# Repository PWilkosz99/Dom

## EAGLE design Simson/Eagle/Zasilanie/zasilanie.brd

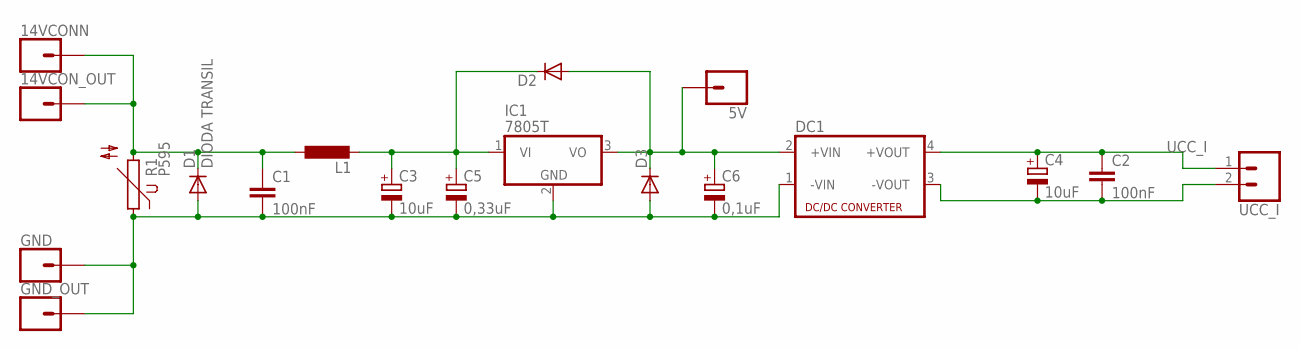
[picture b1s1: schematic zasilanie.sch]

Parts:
5V, 14VCONN, 14VCON_OUT: CONN_01PTH_LONGPAD; 1X01_LONGPAD
C1, C2: 100nF; C025-024X044
C3, C4: 10uF; E2,5-7
C5: 0,33uF; E2,5-7
C6: 0,1uF; E2,5-7
D1: DIODA TRANSIL; DO41-10
D2, D3: 1N4004; DO41-10
DC1: NME
GND: CONN_01PTH_LONGPAD; 1X01_LONGPAD
GND_OUT: CONN_01PTH_LONGPAD; 1X01_LONGPAD
IC1: 7805T; TO220H
L1: L-EUTJ6-U1; TJ6-U1
R1: P595
UCC_I: CONN_02LOCK; 1X02_LOCK

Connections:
GND: C1.2, C3.-, C5.-, C6.-, D1.A, D3.A, DC1.1 (-VIN), GND.1, GND_OUT.1, IC1.2 (GND), R1.1
GND_I: C2.2, C4.-, DC1.3 (-VOUT), UCC_I.2
unnamed: C3.+, C5.+, D2.C, IC1.1 (VI), L1.2
unnamed: 5V.1, C6.+, D2.A, D3.C, DC1.2 (+VIN), IC1.3 (VO)
unnamed: 14VCONN.1, 14VCON_OUT.1, C1.1, D1.C, L1.1, R1.2
UCC_I: C2.1, C4.+, DC1.4 (+VOUT), UCC_I.1

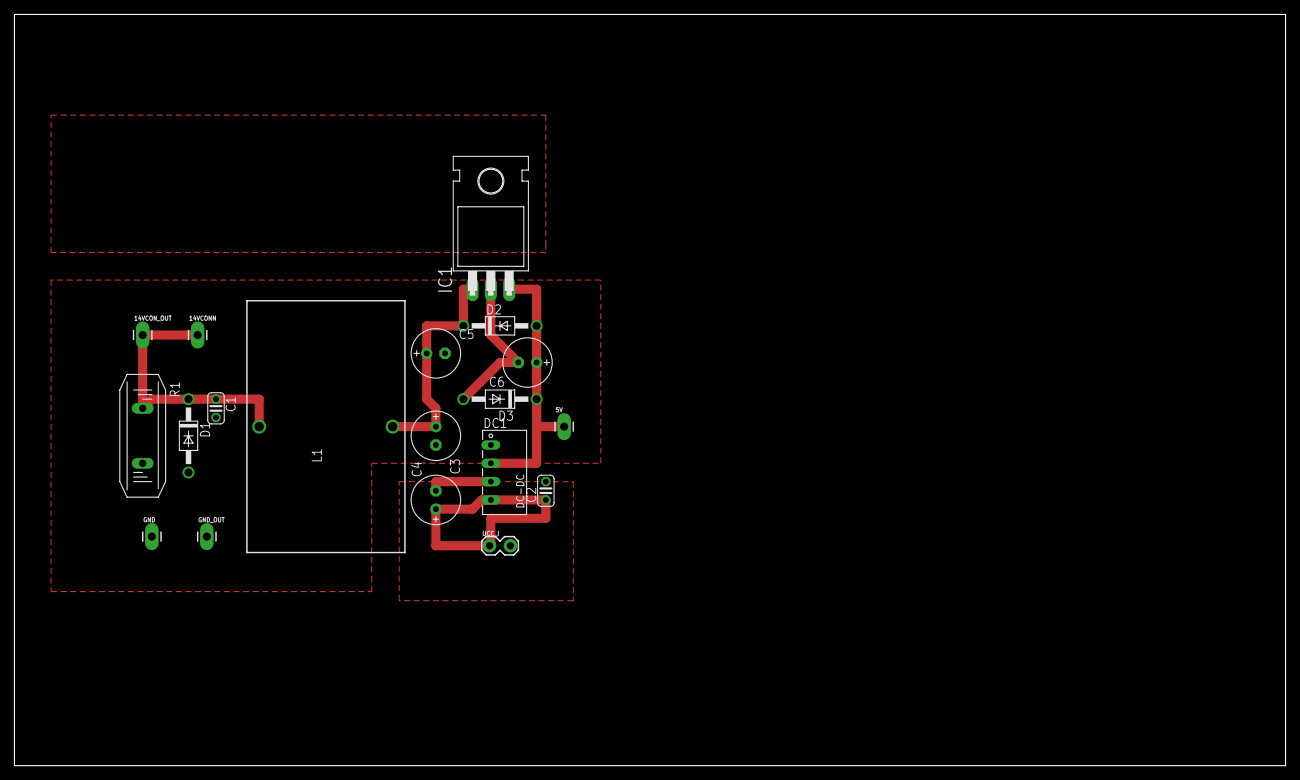
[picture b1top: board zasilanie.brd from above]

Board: 2 copper layers, 176.2 x 104.1 mm, 19 parts (0 on the bottom side), 6 nets.

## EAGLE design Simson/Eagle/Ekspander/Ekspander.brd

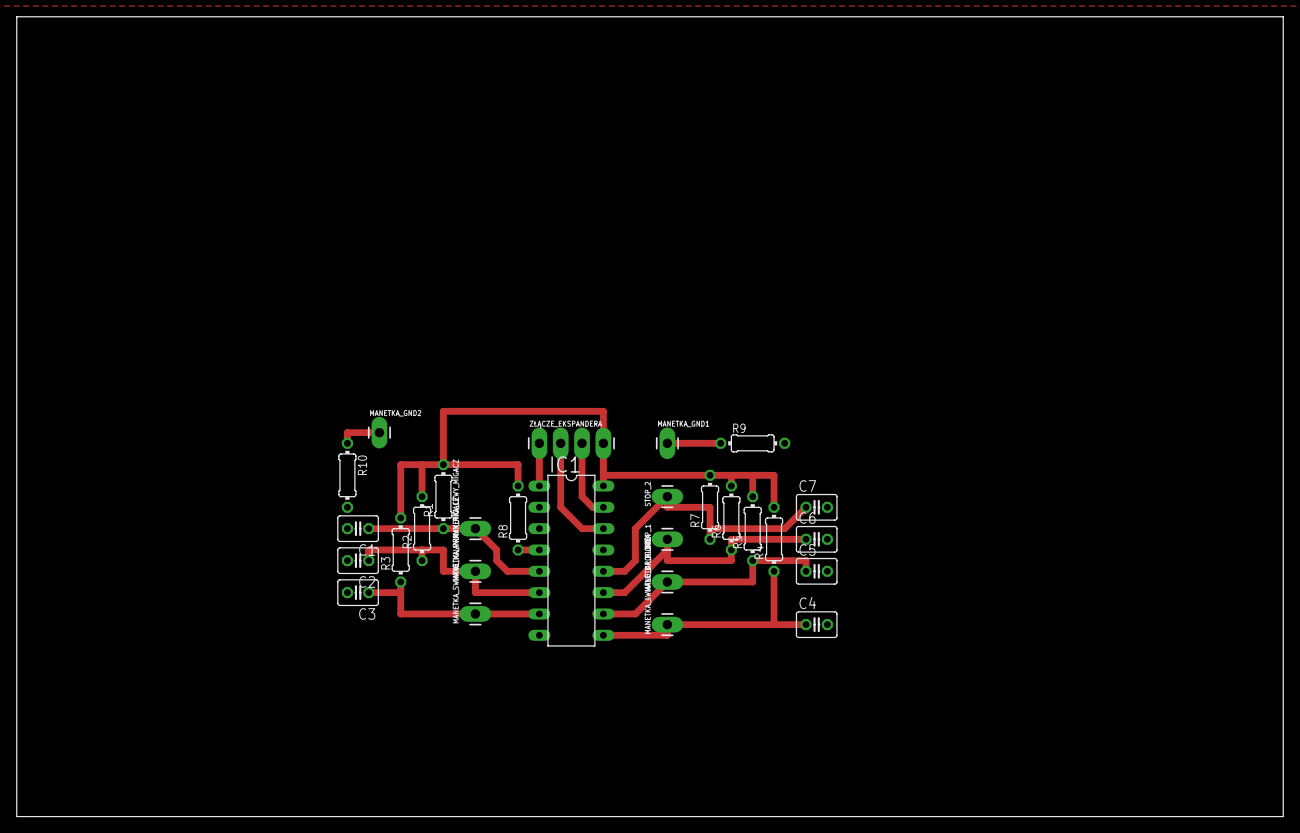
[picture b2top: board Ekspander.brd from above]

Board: 2 copper layers, 150.8 x 95.2 mm, 28 parts (0 on the bottom side), 14 nets.

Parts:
C1, C2, C3, C4, C5, C6, C7: C025-030X050
IC1: PCF8574P; DIL16
MANETKA_BLINDA: 1X01_LONGPAD
MANETKA_GND1, MANETKA_GND2: 1X01_LONGPAD
MANETKA_LEWY_MIGACZ: 1X01_LONGPAD
MANETKA_PRAWY_MIGACZ: 1X01_LONGPAD
MANETKA_SWIATłO_MIJANIA: 1X01_LONGPAD
MANETKA_śWIATLO_DROGOWE: 1X01_LONGPAD
R1, R2, R3, R4, R5, R6, R7, R8: 0204/7
R9, R10: 330 ohm; 0204/7
STOP_1, STOP_2: 1X01_LONGPAD
ZŁĄCZE_EKSPANDERA: 1X04_LONGPADS

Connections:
0: IC1.4, R8.1
1: C1.1, IC1.5, MANETKA_LEWY_MIGACZ.1, R1.1
2: C2.1, IC1.6, MANETKA_PRAWY_MIGACZ.1, R2.1
3: C3.1, IC1.7, MANETKA_SWIATłO_MIJANIA.1, R3.1
4: C4.1, IC1.9, MANETKA_śWIATLO_DROGOWE.1, R4.1
5: C5.1, IC1.10, MANETKA_BLINDA.1, R5.1
5V_I: IC1.16, R1.2, R2.2, R3.2, R4.2, R5.2, R6.2, R7.2, R8.2, ZŁĄCZE_EKSPANDERA.4
6: C6.1, IC1.11, R6.1, STOP_1.1
7: C7.1, IC1.12, R7.1, STOP_2.1
GND_I: C1.2, C2.2, C3.2, C4.2, C5.2, C6.2, C7.2, IC1.1, IC1.2, IC1.3, IC1.8, R9.2, R10.2, ZŁĄCZE_EKSPANDERA.1
unnamed: MANETKA_GND1.1, R9.1
unnamed: MANETKA_GND2.1, R10.1
SCL: IC1.14, ZŁĄCZE_EKSPANDERA.2
SDA: IC1.15, ZŁĄCZE_EKSPANDERA.3

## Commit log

2018-09-04 Dodaj pliki .gitignore i .gitattributes.
2018-09-04 Dodaj pliki projektów.
2018-09-07 2nd changes
2018-09-16 Dodanie Projektu Serwer z UI
2018-10-08 Serwer w wersji z UI, do poprawy m.in Log
2018-10-08 Dodano SerwerRoot w wersji UI Log do poprawy
2018-10-08 Problemy z wersją dot net
2018-10-08 Zminiono obsługę bazy danych sqplite
2018-10-30 Poprawna implementacja podzespoly body
2018-10-30 wczesna wersja binding danych w page settings
2018-11-01 Interakcja UI ustawien z funkcjami
2018-11-04 Do poprawy funkcjonalność modulesbosy.start stop LogPage nie odswieza na bieżaco
2019-01-16 Poprawiono obsługe log.cs oraz zarządzanie modułami przez CancelationToken
2019-01-22 Naprawiono komunikację USB

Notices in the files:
parts and their libraries:
SparkFun-Connectors: Licensing: Creative Commons ShareAlike 4.0 International - https://creativecommons.org/licenses/by-sa/4.0
